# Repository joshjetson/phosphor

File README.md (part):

<p align="center">

</p>

<p align="center">
  <strong>A terminal-native DAW built in Rust</strong><br/>
  9 built-in synthesizers, 18 drum kits, a sampler, 1,531 patches, 9 color themes, animated splash screen, session save/load, undo/redo, and a plugin system designed for extensibility.
</p>

<p align="center">
  <br/>
  <sub><em>an animated impression of the track view — the real thing runs in your terminal:</em></sub>
</p>

---

## Index

- [Overview](#overview)
- [Quick Start](#quick-start)
- [Instruments](#instruments)
- [Features](#features)
- [Sampler — a sound on every key](#sampler--a-sound-on-every-key)
- [Fingers — the practice room](#fingers--the-practice-room)
- [The Phosphor Deck — an optional controller](#the-phosphor-deck--an-optional-controller)
- [Shortcuts, A to Z](#shortcuts-a-to-z)
- [Controls](#controls)
- [Themes](#themes)
- [Architecture](#architecture)
- [Building from Source](#building-from-source)
- [Project Structure](#project-structure)
- [Configuration](#configuration)
- [Contributing](#contributing)
- [License](#license)

---

## Overview

Phosphor is a digital audio workstation that runs entirely in your terminal. It pairs a themeable TUI with a real-time audio engine, giving you a DAW you can use over SSH, in a tiling window manager, or anywhere a terminal lives.

Each instrument track gets its own synthesizer instance with independent parameters. Every MIDI device you plug in is used at once, including ones plugged in while it runs. The audio engine runs on a dedicated real-time thread with lock-free communication — no mutexes in the audio path, ever.

---

## Quick Start

Phosphor runs on Windows, macOS and Linux. Everything is installed with
one command — but that command needs the Rust toolchain, and each
platform has one thing to do first. Start with yours:

**Windows** — install Rust from [rustup.rs](https://rustup.rs). The
installer will say it needs the Visual Studio C++ Build Tools and offer
to set them up — say yes; Rust compiles through them on Windows and
nothing works without them. Then open **Windows Terminal** (built into
Windows 11, free in the Microsoft Store on 10) rather than the old
Command Prompt: Phosphor draws its keyboards, meters and braces in
Unicode, and the legacy console mangles them. Audio and MIDI work out of
the box. Your files land in `%APPDATA%\phosphor`.

**macOS** — if you have never compiled anything on this machine, run
`xcode-select --install` once and let it finish. Then install Rust from
[rustup.rs](https://rustup.rs). Your files land in `~/.phosphor`.

**Linux** — install Rust from [rustup.rs](https://rustup.rs), plus the
ALSA headers the audio layer compiles against — without them the install
command fails halfway with a wall of C errors. Debian/Ubuntu:
`sudo apt install build-essential pkg-config libasound2-dev`. Fedora:
`sudo dnf install alsa-lib-devel`. Arch: `sudo pacman -S alsa-lib`.
Your files land in `~/.phosphor`.

Then, on every platform, the same command — and after it finishes, the
program is simply `phosphor` in your terminal:

```bash
# Install from crates.io — the --locked flag is required. It builds with
# the exact dependency versions the release was tested with; without it
# cargo picks newer ones, which now demand a newer Rust than the crate's,
# and the build fails.
cargo install phosphor-studio --locked

# Then run it
phosphor

# Or clone and build — this is how to get the newest version, which may
# be ahead of the one published on crates.io
git clone https://github.com/joshjetson/phosphor.git
cd phosphor
cargo install --path . --locked

# Run (TUI is the default)
cargo run --release

# Run with debug logging (PowerShell on Windows:
#   $env:PHOSPHOR_DEBUG=1; cargo run --release)
PHOSPHOR_DEBUG=1 cargo run --release

# Run without audio (UI development)
cargo run --release -- --no-audio

# Run without MIDI
cargo run --release -- --no-midi
```

**First steps once running:**

1. Press `Space` to open the command menu
2. Press `a` to add an instrument track
3. Select an instrument and press `Enter`
4. Play your MIDI controller — sound comes out
5. Use `j/k` to navigate synth parameters, `h/l` to adjust values — the
   first one is the patch selector
6. Press `Tab` to reach `[inst]`, the instrument's full panel, laid out in
   columns with room for all of it; `Tab` again for the piano roll
7. Press `Space` then `v` to change the color theme

### Plugging in MIDI gear

Plug in as many MIDI keyboards and controllers as you like — Phosphor
listens to all of them at once. You can plug one in or pull it out while
Phosphor is running: within a couple of seconds the bottom bar says
`MIDI: <name> connected` (or `unplugged`), and it just works. Nothing to set
up, no restart.

### Staying up to date

The first time you run a version you have not seen, phosphor shows a
**what's new** card — a short note on what changed, scrollable with `j`/`k`,
closed with `Esc` or `Enter`. It reads the same summaries kept in
[`CHANGELOG.md`](CHANGELOG.md).

Phosphor also checks crates.io in the background — at most once every six
hours, and silently if you are offline — and if a newer version is published
it shows a single line in the bottom bar telling you the one command that
updates it: `cargo install phosphor-studio --locked`. Press `Esc` at the track
list to dismiss it. To turn the check off entirely, set
`PHOSPHOR_NO_UPDATE_CHECK=1` in your environment.

### Will my computer keep up? — `phosphor --benchmark`

Run `phosphor --benchmark` on any computer — a laptop, a Raspberry Pi —
before you rely on it for music. It plays a busy song (every instrument,
effects, sends and a loop recording) through Phosphor's real sound engine
for about half a minute, first on one core and then on all of them, and
times every block of sound against the time it has. Then it says, in a
sentence, whether that computer has plenty of room, keeps up, or will
break up on a song that heavy. Close other busy programs first: anything
else using the processor makes the result look worse than it is.

---

## Instruments

### Synthesizers

| Instrument | Type | Voices | Patches | Description |
|-----------|------|--------|---------|-------------|
| **Phosphor Synth** | Wavetable / vector | 8 | **229** | Four oscillators with vector mixing, 16 wavetables, per-oscillator wave sequencing, Moog-style ladder, 6-slot mod matrix, keymapped drum patches |
| **DX7** | FM | 16 | **256** | All 8 original factory cartridges, decoded from the ROM dumps |
| **Jupiter-8** | Analog poly | 8 | **64** | All 64 factory patch names, full 32-control panel, two envelopes |
| **ARP Odyssey** | Duophonic | 2 | 44 | Complete 59-control front panel, all three filter revisions (4023/4035/4075), ADSR *and* AR envelopes, sample and hold |
| **Rhodes** | Physical model | 16 | 26 | Tine and tonebar as a coupled fork, inharmonic cantilever modes, nonlinear magnetic pickup |
| **Juno-60** | DCO poly | 6 | **56** | All 56 factory patches, read off Roland's patch charts; complete 25-control front panel measured against the hardware |
| **Little Phatty** | Mono Moog | 1 | **100** | Continuously morphing oscillators (triangle→saw→square→pulse, band-limited at every position in between), hard sync, 1/2/3/4-pole ladder, pre- and post-filter overload, the one-bus mod matrix with its spare destination, glide, and the three keyboard priorities |
| **Prophet-6** | Analog poly | 6 | **500** | All 500 factory programs, decoded from Sequential's own SysEx. Morphing oscillators with a triangle sub, resonant high-pass *and* SSM2040-lineage low-pass in series, poly mod (filter envelope and oscillator 2 into oscillator 1's frequency, shape and width and into both filters, at audio rate), per-oscillator slop, unison with chord memory, aftertouch, analog distortion |
| **TEO-5** | Analog poly | 5 | **256** | All 256 factory programs, decoded from Oberheim's own SysEx. The SEM state-variable filter, whose state control morphs continuously from low pass through notch to high pass with band pass on a switch; through-zero FM between the oscillators; three independently mixable waveshapes each, hard sync, a square sub and white or pink noise; two OB-8-curve DADSR envelopes; a global LFO and a per-voice one; a 16-slot modulation matrix of 20 sources against 65 destinations; twelve effect algorithms; unison with stored chord memory |

### Sampler

| Instrument | Type | Voices | Sounds | Description |
|-----------|------|--------|--------|-------------|
| **Sampler** | Sample playback | 64 | yours | 88 pads, one per piano key, eight sounds stacked on each with their own tune, trim, reverse and mute; per-pad trigger, poly, choke group, round robin, pitch, ADSR, level, pan, root and keytracking; a trim strip with a zero-crossing snap and a key that
hugs the sound; **keys mode**, where stretches of keys become chromatic zones playing one sound from a root; and resampling — record any instrument in the box onto a pad, free or cut to whole bars; and **chop** — cut a recording across the keys at its hits (kicks, snares or hats), on a beat grid, or into even slices |

64 is the number of voices allowed to sound at once, across the whole
instrument rather than per pad; the pool behind it holds 80, so a voice that
gets cut has somewhere to finish its fade. The per-pad limit is `poly`, which
runs 1–8 and counts *hits*.

### Drum Rack

| Kit | Character |
|-----|-----------|
| **808** | Rebuilt on the service-notes circuit values — 49.4 Hz bridged-T kick, 238/476 Hz snare, one shared free-running six-oscillator metal bank |
| **909** | The hybrid it really is — analog kick/snare/toms/rim/clap, and hi-hat, ride and crash as 6-bit 18 kHz samples |
| **707** | A PCM machine, not an analog one — sampled character through post-converter analog envelopes |
| **606** | Its own seven analog voices, built from the service-notes component values |
| **777** | 808/909 bass + creative FM/ring-mod/wavefolder sounds |
| **tsty-1** | Warm vintage, tape-saturated, reel-to-reel character |
| **tsty-2** | Acoustic modal — Bessel membrane modes, multi-phase envelopes |
| **tsty-3** | 88 unique sounds — every note a distinct synthesis |
| **tsty-4** | Extended hats/snares with long decays, varied synthesis methods |
| **tsty-5** | Resonator-based — impulse exciter into tuned bandpass filters, wire-coupled snares |
| **LinnDrum** | 15 recordings through a mu-255 companded 8-bit converter; tuning is the read clock, so pitch and length move together |
| **DMX** | 11 recordings making 15 sounds, companded 8-bit, per-card pitch trimmer at half an octave |
| **SDS-V** | Five analog modules — triangle VCO, noise and click through a 4-pole SSM2044, ramp VCAs that stop rather than fade |
| **727** | The 707's converter with the Latin voice set: congas, bongos, timbales, agogo, cabasa, maracas, whistles, quijada, star chime |
| **CR-78** | Pre-808 Roland analog — a snare with no oscillator in it at all, one LC band-pass for every metal voice, and the metallic beat |
| **jazz** | Live acoustic drums, modelled — a small bebop kit: sealed 18" kick with the two heads coupled through the shell, thin heads left to ring, a dark 20" ride, and brushes |
| **funk** | The same physics, a different drummer — 22" ported kick with a felt strip, a cranked snare over twenty tight strands, gel on the toms, and a ride with a ping |
| **studio** | Very dry and gated — a pillow in the kick that all but closes the two-head coupling, a muffling ring on the snare, taped toms, and a downward expander across every voice |

Past `studio`, the `kit` knob goes on into drum kits you made yourself on a
sampler — see [Your own drum kits](#your-own-drum-kits--spacew-on-a-sampler).

### Patch Highlights

**DX7** (256 voices): every voice from the eight original factory cartridges —
ROM1A/1B, ROM2A/2B, ROM3A/3B, ROM4A/4B — decoded from the ROM sysex dumps rather
than recreated. That includes the ones that defined the instrument: `E.PIANO 1`,
`BASS    1`, `TUB BELLS`, `BRASS   1`, `STRINGS 1`, `HARPSICH 1`, and the novelty
voices Yamaha shipped alongside them (`TAKE OFF`, `WASP STING`, `..GOTCHA..`).
Pick a cartridge with the `bank` parameter, then a voice with `patch`.

**Jupiter-8** (64 patches): the factory bank in Roland's own 8x8 numbering — `11 NEG SYNC`,
`13 JUICY FUNK`, `15 CARS SYNC`, `17 HAMMER LEAD`, `24 MELLOW RHODES`, `31 LO STRINGS`,
`45 PIPE ORGAN`, `51 TRAIN CHUG`, `57 TOMITA CHIME`, `63 KLINGONS`, `64 MUSIC OF THE SPHERES`,
`66 SOLAR WINDS`, `71 FAT FIFTHS`, `87 UPRIGHT BASS` and the rest. Names, numbers, voice modes
and character follow the original factory patch sheets; the parameter values are voiced to match
Roland's published description of each patch.

**Odyssey** (44 patches): Bass, Funk, Sync Lead, Bells, Pad, S&H, Zap, Hawkshaw Funk, Bennett Atmos, Numan Cars, Sci-Fi Wobble, Percussive Pluck, Thick Lead, Filter Sweep, Noise Hit, Duo Split, Snare Drum, Kick, Resonance, Squelch, Growl, Wind, Wah Bass, Stab, Buzz, Flute, Tremolo, Siren, Brass, Organ, Conga, Tom, Clap, PWM Bass, Violin, Oboe, Choir, Trombone, Marimba, Alarm, Robot, Whistler, Sitar, Theremin

**Juno-60** (56 factory patches, in the instrument's own seven banks of eight):

- **Bank 1** — 11 Strings 1, 12 Strings 2, 13 Strings 3, 14 Organ 1, 15 Organ 2, 16 Organ 3, 17 Brass, 18 Phase Brass
- **Bank 2** — 21 Piano 1, 22 Piano 2, 23 Celesta, 24 Mellow Piano, 25 Harpsichord 1, 26 Harpsichord 2, 27 Guitar, 28 Synthesizer Harp
- **Bank 3** — 31 Bass 1, 32 Bass 2, 33 Clavichord 1, 34 Clavichord 2, 35 Pizzicato Sound 1, 36 Pizzicato Sound 2, 37 Xylophone, 38 Glockenspeil
- **Bank 4** — 41 Violine, 42 Trumpet, 43 Horn, 44 Tuba, 45 Flute, 46 Clarinet, 47 Oboe, 48 English Horn
- **Bank 5** — 51 Funny Cat, 52 Wah Brass, 53 Phase Combination, 54 Reed 1, 55 Popcorn, 56 Reed 2, 57 Reed 3, 58 PWM Chorus
- **Bank 6** — 61 Synthesizer Organ, 62 Effect Sound 1, 63 Effect Sound 2, 64 Space Harp, 65 Funk, 66 Space Sound 1, 67 Mysterious Invention, 68 Space Sound 2
- **Bank 7** — 71 Percussive Sound 1, 72 Percussive Sound 2, 73 Whistle, 74 Effect Sound 3, 75 UFO, 76 Space Sound 3, 77 Surf, 78 Synthesizer Drum — the bank whose sound source is the VCF oscillating on its own

Names and spellings are Roland's, Glockenspeil included.

**Little Phatty** (100 patches, ours rather than Moog's — the Stage II's factory
*names* are printed in its manual but no published source gives the parameter
values behind them, so the bank is original and named in our own voice, weighted
towards bass the way the real one is):

- **Moog bass** — Taurus Deep, Sub Anchor, Round Bass, Bass Pillar, Thumb Bass, Wood Bass, Rubber Bass, Octave Bass, Muted Bass, Fifth Bass, Tri Sub, Pulse Bass, Sine Floor, Dub Weight, Slide Bass, Sequence Lo, Fat Unison, Bass Bloom
- **Overload** — Growl Bass, Tarmac, Coal Face, Snarl, Fuzz Anchor, Grit Stack, Overdriven, Bark Bass, Diesel, Torn Paper, Anvil Bass, Bad Weather
- **Sync** — Sync Lead, Sync Scream, Sync Sweep, Hard Reset, Sync Bell, Sync Buzz, Sync Whistle, Sync Stab
- **Lead** — Solo Saw, Reed Lead, Glass Lead, Whistle Top, Portamento, Brass Lead, Ribbon Lead, Flute Solo, Nasal Lead, Octave Lead, Vox Lead, Cut Lead
- **Wave morph** — Morph Drift, Half Saw, Between, Wave Wash, Slow Morph, Pulse Width, PWM Strings, Thin Ice, Wave Chase, Shape Shift, Morph Bass, Tri To Saw
- **Sample and hold, and effects** — Random Steps, Sample Hold, Computer, Alarm, Siren, Radio Chirp, Wind Tunnel, Static, Bleep Bloop, Sonar
- **Slope** — 2 Pole Bass, 1 Pole Pad, Open Ladder, Leaky, Bright 12dB, 6dB Lead, Half Ladder, Slope Swap
- **Pluck and percussion** — Zap Pluck, Clav Pluck, Wood Block, Kick Drum, Tom Hit, Blip, Marimba, Snap Bass, Dry Tick, Bell Pluck
- **Drone** — Self Osc, Slow Swell, Held Tone, Deep Drone, Air Pad, Ghost Pad, Filter Wash, Long Fifth, Choir Mono, Night Hum

**Rhodes** (26 patches, by instrument rather than by factory number — a Rhodes
has no patch memory):

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
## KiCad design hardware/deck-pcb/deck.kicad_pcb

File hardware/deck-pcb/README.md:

# Phosphor Deck controller board

The circuit board for the Phosphor Deck: every knob, button, fader and pad on
top, and the electronics that read them underneath. It is the board drawn on
the schematics, and it runs the firmware in [`../../firmware`](../../firmware).

**Rev A has not been made yet.** It passes KiCad's design-rule check with no
errors and no unconnected pins, but nobody has held one. Build the breadboard
test in the firmware's README before ordering.

## What to send a board house

Everything is in `fab/`:

- `gerbers.zip` — the board itself: two copper layers, 296 × 234 mm, 1.6 mm.
- `bom.csv` — every part, grouped, with the part to buy where there is one.
- `positions-bottom.csv` — where each surface-mount part goes, for a house
  that assembles the underside.
- `jlc-bom.csv` and `jlc-cpl.csv` — the same parts and places in the exact
  form JLCPCB asks for, with their LCSC part numbers.

The board is laid out so that a board house only has to assemble one side:
every surface-mount part (chips, resistors, capacitors, LEDs, the Pico 2) is
on the bottom. Everything on top is through-hole and soldered by hand: 61
switches, 10 knobs, 8 faders, the 16 pad sensors' tabs and the pedal header.

## Ordering from JLCPCB, step by step

JLCPCB makes the board and solders every part on the underside for you. You
then solder the top parts by hand.

1. **Upload the board.** On jlcpcb.com, choose *Order now* and add
   `fab/gerbers.zip`. It reads the size (296 × 234 mm) and the two layers by
   itself.
2. **Choose the board options.** Layers 2, thickness 1.6 mm, FR-4. Five
   boards is the smallest order. Green is the cheapest colour; any colour
   works. For the surface finish, lead-free HASL is fine; ENIG costs more
   and gives flatter pads. Leave the rest as it is.
3. **Turn on PCB Assembly.** Choose:
   - *PCBA type: Standard.* Economic is cheaper, but it is meant for one
     side, usually the top, and JLC sells the Pico 2 for Standard only. If
     Economic offers *Bottom Side* when you order and you will solder the
     Pico yourself, Economic works too.
   - *Assembly side: Bottom Side.* Every machine part is underneath.
   - *Assembly quantity:* 2 or more; it can be fewer than the boards.
   - Let JLC add the edge rails, fiducials and tooling holes if it asks.
     Standard assembly needs them and the board has none of its own.
   - Tick *Confirm parts placement*: for a small fee, one of their engineers
     checks the placements and asks you before building.
4. **Upload the two parts files**: `fab/jlc-bom.csv` as the BOM and
   `fab/jlc-cpl.csv` as the CPL (the placement file). Every line should
   match a part. If one is out of stock, pick a part with the same value,
   rating and size, or wait.
5. **Check the placement preview.** It shows each part on the board, seen
   from underneath. The files already turn each part the way JLC's drawings
   need, but look at each kind once:
   - the chips (U1–U16): the dot that marks pin 1 sits on the board's pin-1
     mark;
   - the LEDs (D1–D42): the LED's cut corner matches its outline, and the
     body sits over the light hole;
   - the big capacitor (C79): its + side sits on the + pad;
   - the Pico 2 (U15): its USB socket is at the same end as on the board
     drawing.

   The small resistors and capacitors can sit either way round. If a part
   is wrong, select it and turn it in the preview, or change its *Rotation*
   in `jlc-cpl.csv` and upload it again.
6. **Solder the top by hand** when the boards arrive: the 61 switches, 10
   knobs, 8 faders, the 16 pad sensors' tabs and the pedal header. If you
   left the Pico 2 off the order (mark it *do not place* on the parts page),
   solder it underneath by its edge pads.

The board is larger than 650 cm², so JLC adds a large-board fee to the
assembly. Basic parts need no loading fee in an Economic order; in a
Standard order every kind of part has a small one.

## Things to know before ordering

- **The LED light holes.** The LEDs sit underneath and shine up through small
  holes. KiCad's own footprint for them puts their pads 0.25 mm from the
  hole's corners; the rest of the board keeps 0.3 mm. Most board houses accept
  this for internal cutouts — ask yours.
- **The buttons are 6 × 6 mm tactile switches** under printed caps, because
  the panel's buttons sit closer together than keyboard switches allow. Pick
  the switch height that meets your caps through the top plate.
- **The faders are centred at 167 mm**, 2 mm lower than the first panel
  drawing: a PTA4543's body is 60 mm long. The top plate's slots run from
  143 to 191 mm.
- **Lights on narrow buttons are dots.** The transport and function buttons
  are too narrow for a light inside the cap, so theirs sits just above as a
  dot in the top plate.
- **The Pico 2 is soldered flat by its edges** on the underside. Its USB
  socket points along the board, so use a right-angle micro-USB cable to the
  Raspberry Pi.

## Making it again

The board is generated, not drawn: `generate.py` places every part from the
panel drawing and wires it from `firmware/deck-layout.json`, Phosphor's own
control table, so the board, the firmware and the app share one table.
`route.sh` runs the lot — placement, routing with Freerouting, ground pours,
the design-rule check, and the files in `fab/`:

```
KICAD=/Applications/KiCad/KiCad.app \
FREEROUTING=freerouting-2.4.1.jar \
JAVA=<a Java 25 runtime>/bin/java \
./route.sh
```

It needs KiCad 10 and Freerouting 2.4, which needs Java 25. Routing takes
about five minutes a try. The router's result varies a little from run to
run and now and then leaves a connection unrouted, so the script tries up to
three times and writes `fab/` only from a board with no errors and nothing
unconnected; `drc.rpt` is the check that board passed. A ground fill covers
both sides, tied together by stitching vias wherever one fits.

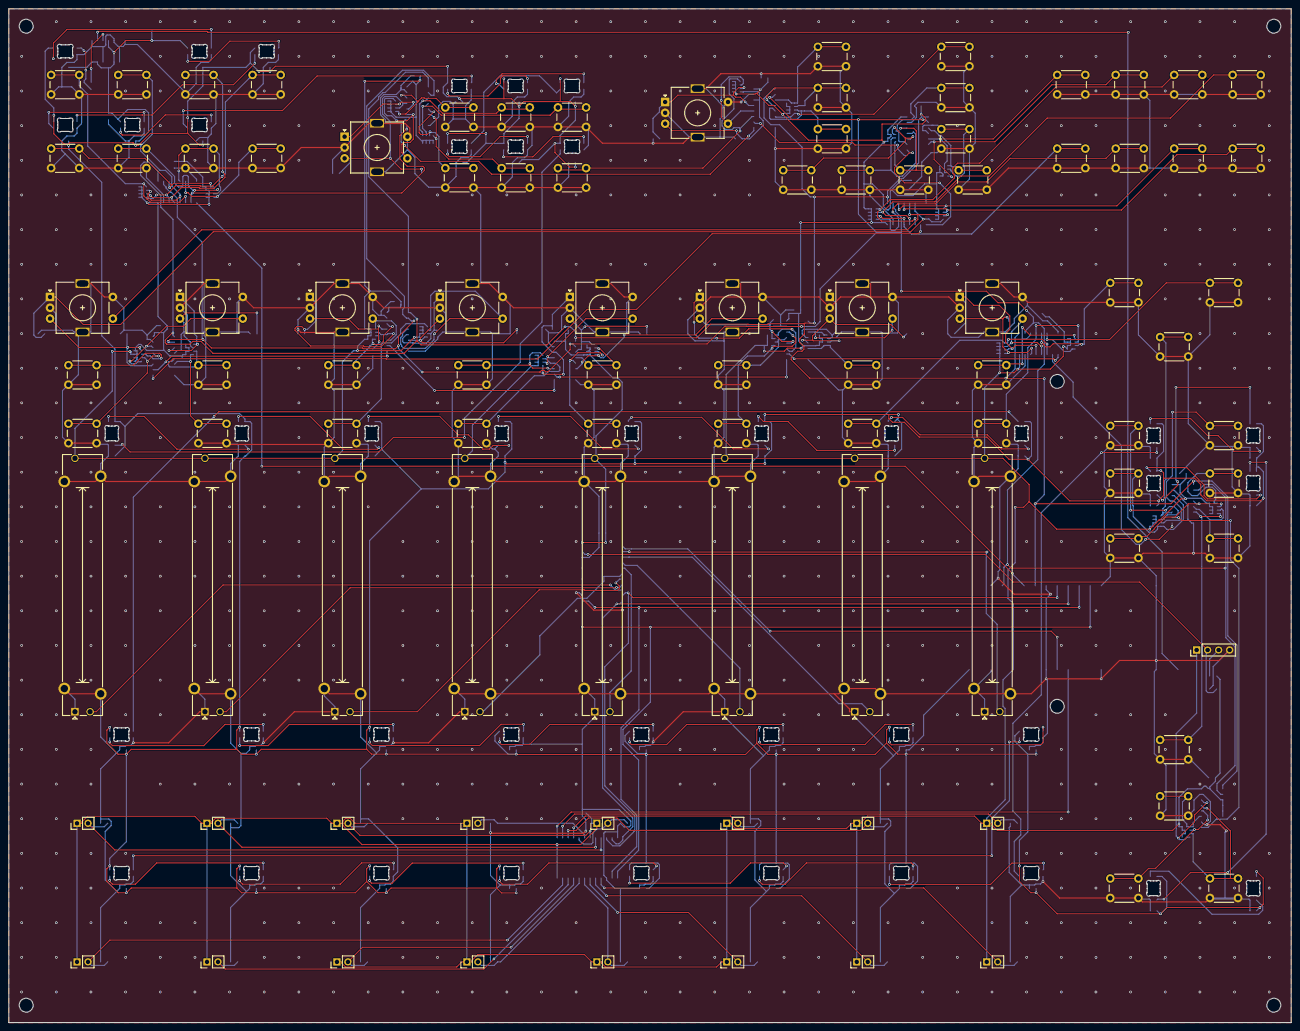
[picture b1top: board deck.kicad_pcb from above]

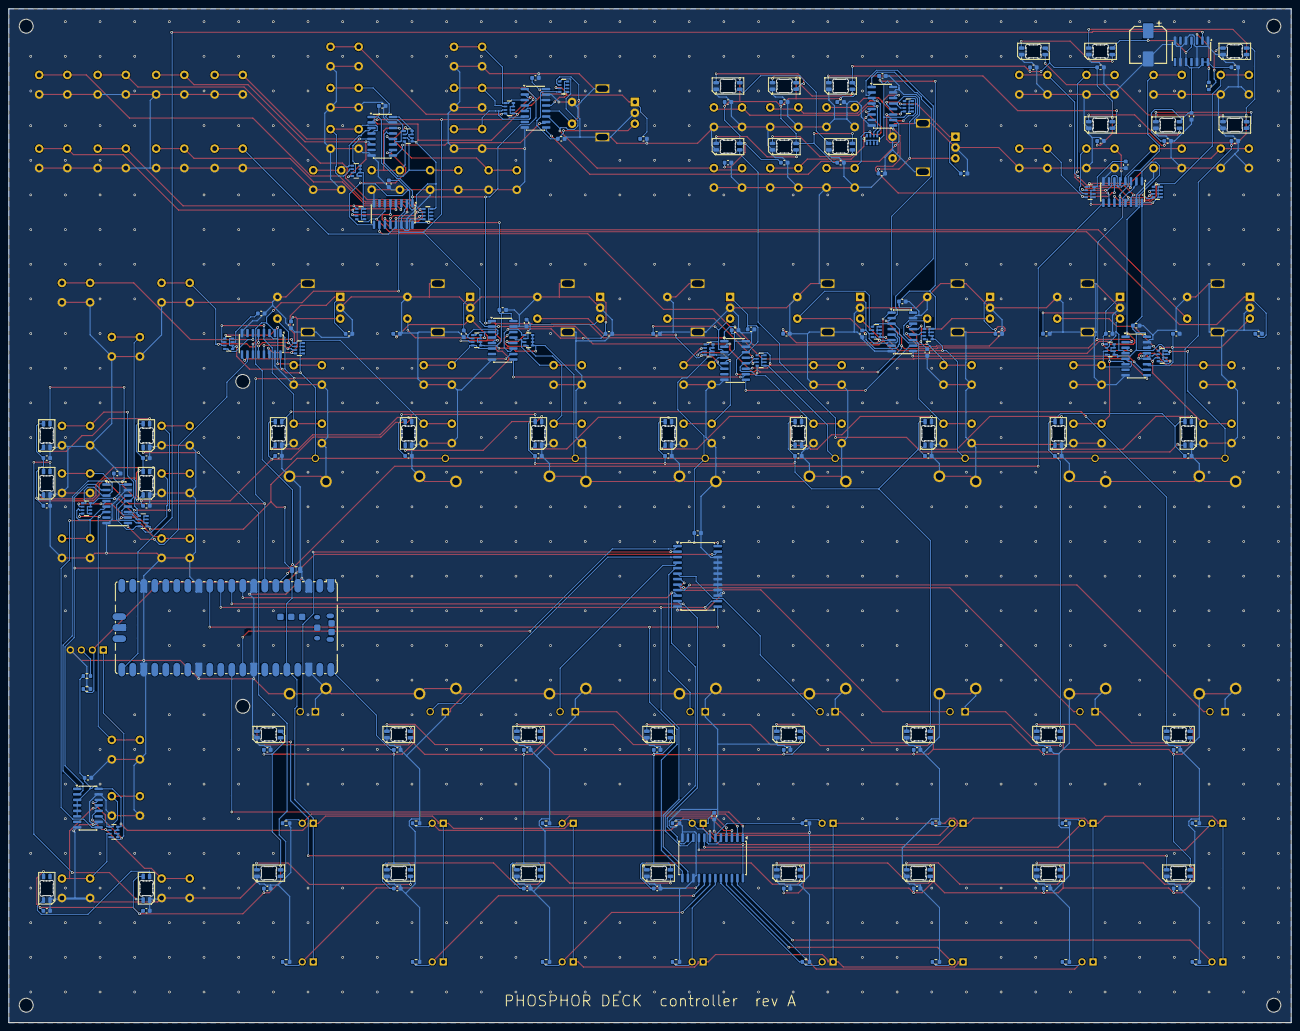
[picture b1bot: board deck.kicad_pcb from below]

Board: 2 copper layers, 296.0 x 234.0 mm, 281 parts (179 on the bottom side), 185 nets.

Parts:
C1, C2, C3, C4, C5, C6, C7, C8, C9, C10, C11, C12, C13, C14, C15, C16, C17, C18, C19, C20, C21, C22, C23, C24, C25, C26, C27, C28, C29, C30, C31, C32, C33, C34, C35, C36, C37, C38, C39, C40, C41, C42, C43, C44, C45, C46, C47, C48, C49, C50, C51, C52, C53, C54, C75, C76, C78: 100n; C_0603_1608Metric
C55, C56, C57, C58, C59, C60, C61, C62, C63, C64, C65, C66, C67, C68, C69, C70, C71, C72, C73, C74: 10n; C_0603_1608Metric
C77: 10u; C_0805_2012Metric
C79: 1000u 10V; CP_Elec_8x10
D1, D2, D3, D4, D5, D6, D7, D8, D9, D10, D11, D12, D13, D14, D15, D16, D17, D18, D19, D20, D21, D22, D23, D24, D25, D26, D27, D28, D29, D30, D31, D32, D33, D34, D35, D36, D37, D38, D39, D40, D41, D42: SK6812MINI-E; LED_SK6812MINI-E_3.2x2.8mm_P1.5mm_ReverseMount
ENC1: FUNCTION; RotaryEncoder_Alps_EC11E-Switch_Vertical_H20mm
ENC2: NAVIGATE; RotaryEncoder_Alps_EC11E-Switch_Vertical_H20mm
ENC3: KNOB 1; RotaryEncoder_Alps_EC11E-Switch_Vertical_H20mm
ENC4: KNOB 2; RotaryEncoder_Alps_EC11E-Switch_Vertical_H20mm
ENC5: KNOB 3; RotaryEncoder_Alps_EC11E-Switch_Vertical_H20mm
ENC6: KNOB 4; RotaryEncoder_Alps_EC11E-Switch_Vertical_H20mm
ENC7: KNOB 5; RotaryEncoder_Alps_EC11E-Switch_Vertical_H20mm
ENC8: KNOB 6; RotaryEncoder_Alps_EC11E-Switch_Vertical_H20mm
ENC9: KNOB 7; RotaryEncoder_Alps_EC11E-Switch_Vertical_H20mm
ENC10: KNOB 8; RotaryEncoder_Alps_EC11E-Switch_Vertical_H20mm
FSR1: PAD 1; PinHeader_1x02_P2.54mm_Vertical
FSR2: PAD 2; PinHeader_1x02_P2.54mm_Vertical
FSR3: PAD 3; PinHeader_1x02_P2.54mm_Vertical
FSR4: PAD 4; PinHeader_1x02_P2.54mm_Vertical
FSR5: PAD 5; PinHeader_1x02_P2.54mm_Vertical
FSR6: PAD 6; PinHeader_1x02_P2.54mm_Vertical
FSR7: PAD 7; PinHeader_1x02_P2.54mm_Vertical
FSR8: PAD 8; PinHeader_1x02_P2.54mm_Vertical
FSR9: PAD 9; PinHeader_1x02_P2.54mm_Vertical
FSR10: PAD 10; PinHeader_1x02_P2.54mm_Vertical
FSR11: PAD 11; PinHeader_1x02_P2.54mm_Vertical
FSR12: PAD 12; PinHeader_1x02_P2.54mm_Vertical
FSR13: PAD 13; PinHeader_1x02_P2.54mm_Vertical
FSR14: PAD 14; PinHeader_1x02_P2.54mm_Vertical
FSR15: PAD 15; PinHeader_1x02_P2.54mm_Vertical
FSR16: PAD 16; PinHeader_1x02_P2.54mm_Vertical
H1, H2, H3, H4, H5, H6: M3; MountingHole_3.2mm_M3
J1: PEDALS; PinHeader_1x04_P2.54mm_Vertical
R1, R2, R3, R4, R5, R6, R7, R8, R9, R10, R11, R12, R13, R14, R15, R16: 10k; R_0603_1608Metric
R17: 1k; R_0603_1608Metric
R18: 100k; R_0603_1608Metric
R19: 330; R_0603_1608Metric
RN1, RN2, RN3, RN4, RN5, RN6, RN7, RN8, RN9, RN10, RN11, RN12, RN13, RN14, RN15, RN16, RN17, RN18, RN19, RN20, RN21, RN22, RN23: 4x10k; R_Array_Convex_4x0603
RV1: FADER 1; Potentiometer_Bourns_PTA4543_Single_Slide
RV2: FADER 2; Potentiometer_Bourns_PTA4543_Single_Slide
RV3: FADER 3; Potentiometer_Bourns_PTA4543_Single_Slide
RV4: FADER 4; Potentiometer_Bourns_PTA4543_Single_Slide
RV5: FADER 5; Potentiometer_Bourns_PTA4543_Single_Slide
RV6: FADER 6; Potentiometer_Bourns_PTA4543_Single_Slide
RV7: FADER 7; Potentiometer_Bourns_PTA4543_Single_Slide
RV8: FADER 8; Potentiometer_Bourns_PTA4543_Single_Slide
SW1: PLAY; SW_PUSH_6mm
SW2: STOP; SW_PUSH_6mm
SW3: REC; SW_PUSH_6mm
SW4: OVERDUB; SW_PUSH_6mm
SW5, SW13: LOOP; SW_PUSH_6mm
SW6: CLICK; SW_PUSH_6mm
SW7: COUNT IN; SW_PUSH_6mm
SW8: TAP; SW_PUSH_6mm
SW9: TEMPO; SW_PUSH_6mm
SW10: SWING; SW_PUSH_6mm
SW11: GRID; SW_PUSH_6mm
SW12: MASTER; SW_PUSH_6mm
SW14: LAST; SW_PUSH_6mm
SW15: LOCK; SW_PUSH_6mm
SW16: BACK; SW_PUSH_6mm
SW17: BROWSE; SW_PUSH_6mm
SW18: SHIFT; SW_PUSH_6mm
SW19: MENU; SW_PUSH_6mm
SW20: LEFT; SW_PUSH_6mm
SW21: UP; SW_PUSH_6mm
SW22: DOWN; SW_PUSH_6mm
SW23: RIGHT; SW_PUSH_6mm
SW24: PART; SW_PUSH_6mm
SW25: UNDO; SW_PUSH_6mm
SW26: REDO; SW_PUSH_6mm
SW27: COPY; SW_PUSH_6mm
SW28: PASTE; SW_PUSH_6mm
SW29: DELETE; SW_PUSH_6mm
SW30: DUPLICATE; SW_PUSH_6mm
SW31: SAVE; SW_PUSH_6mm
SW32: NEW; SW_PUSH_6mm
SW33: ACTION 1; SW_PUSH_6mm
SW34: T1; SW_PUSH_6mm
SW35: ACTION 2; SW_PUSH_6mm
SW36: T2; SW_PUSH_6mm
SW37: ACTION 3; SW_PUSH_6mm
SW38: T3; SW_PUSH_6mm
SW39: ACTION 4; SW_PUSH_6mm
SW40: T4; SW_PUSH_6mm
SW41: ACTION 5; SW_PUSH_6mm
SW42: T5; SW_PUSH_6mm
SW43: ACTION 6; SW_PUSH_6mm
SW44: T6; SW_PUSH_6mm
SW45: ACTION 7; SW_PUSH_6mm
SW46: T7; SW_PUSH_6mm
SW47: ACTION 8; SW_PUSH_6mm
SW48: T8; SW_PUSH_6mm
SW49: ◀ PG; SW_PUSH_6mm
SW50: PG ▶; SW_PUSH_6mm
SW51: MY PAGE; SW_PUSH_6mm
SW52: SELECT; SW_PUSH_6mm
SW53: MUTE; SW_PUSH_6mm
SW54: SOLO; SW_PUSH_6mm
SW55: ARM; SW_PUSH_6mm
SW56: ◀ TRK; SW_PUSH_6mm
SW57: TRK ▶; SW_PUSH_6mm
SW58: PADS ▲; SW_PUSH_6mm
SW59: PADS ▼; SW_PUSH_6mm
SW60: 1-16; SW_PUSH_6mm
SW61: 17-32; SW_PUSH_6mm
U1, U2, U3, U4, U5, U6, U7, U8, U9, U10, U11, U12: 74HC165; SOIC-16_3.9x9.9mm_P1.27mm
U13, U14: 74HC4067; SOIC-24W_7.5x15.4mm_P1.27mm
U15: Pico 2; RaspberryPi_Pico_SMD
U16: 74AHCT125; SOIC-14_3.9x8.7mm_P1.27mm

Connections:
+3V3: C43.1, C44.1, C45.1, C46.1, C47.1, C48.1, C49.1, C50.1, C51.1, C52.1, C53.1, C54.1, C75.1, C76.1, C77.1, FSR1.1, FSR2.1, FSR3.1, FSR4.1, FSR5.1, FSR6.1, FSR7.1, FSR8.1, FSR9.1, FSR10.1, FSR11.1, FSR12.1, FSR13.1, FSR14.1, FSR15.1, FSR16.1, R17.1, RN1.5, RN1.6, RN1.7, RN1.8, RN2.5, RN2.6, RN2.7, RN2.8, RN3.5, RN3.6, RN3.7, RN3.8, RN4.5, RN4.6, RN4.7, RN4.8, RN5.5, RN5.6, RN5.7, RN5.8, RN6.5, RN6.6, RN6.7, RN6.8, RN7.5, RN7.6, RN7.7, RN7.8, RN8.5, RN8.6, RN8.7, RN8.8, RN9.5, RN9.6, RN9.7, RN9.8, RN10.5, RN10.6, RN10.7, RN10.8, RN11.5, RN11.6, RN11.7, RN11.8, RN12.5, RN12.6, RN12.7, RN12.8, RN13.5, RN13.6, RN13.7, RN13.8, RN14.5, RN14.6, RN14.7, RN14.8, RN15.5, RN15.6, RN15.7, RN15.8, RN16.5, RN16.6, RN16.7, RN16.8, RN17.5, RN17.6, RN17.7, RN17.8, RN18.5, RN18.6, RN18.7, RN18.8, RN19.5, RN19.6, RN19.7, RN19.8, RN20.5, RN20.6, RN20.7, RN20.8, RN21.5, RN21.6, RN21.7, RN21.8, RN22.5, RN22.6, RN22.7, RN22.8, RN23.5, RN23.6, RN23.7, RN23.8, RV1.3, RV2.3, RV3.3, RV4.3, RV5.3, RV6.3, RV7.3, RV8.3, U1.16, U2.16, U3.16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
+5V: C1.1, C2.1, C3.1, C4.1, C5.1, C6.1, C7.1, C8.1, C9.1, C10.1, C11.1, C12.1, C13.1, C14.1, C15.1, C16.1, C17.1, C18.1, C19.1, C20.1, C21.1, C22.1, C23.1, C24.1, C25.1, C26.1, C27.1, C28.1, C29.1, C30.1, C31.1, C32.1, C33.1, C34.1, C35.1, C36.1, C37.1, C38.1, C39.1, C40.1, C41.1, C42.1, C78.1, C79.1, D1.3, D2.3, D3.3, D4.3, D5.3, D6.3, D7.3, D8.3, D9.3, D10.3, D11.3, D12.3, D13.3, D14.3, D15.3, D16.3, D17.3, D18.3, D19.3, D20.3, D21.3, D22.3, D23.3, D24.3, D25.3, D26.3, D27.3, D28.3, D29.3, D30.3, D31.3, D32.3, D33.3, D34.3, D35.3, D36.3, D37.3, D38.3, D39.3, D40.3, D41.3, D42.3, U15.40, U16.4, U16.10, U16.13, U16.14
CHAIN1: U1.10, U2.9
CHAIN2: U2.10, U3.9
CHAIN3: U3.10, U4.9
CHAIN4: U4.10, U5.9
CHAIN5: U5.10, U6.9
CHAIN6: U6.10, U7.9
CHAIN7: U7.10, U8.9
CHAIN8: U8.10, U9.9
CHAIN9: U9.10, U10.9
CHAIN10: U10.10, U11.9
CHAIN11: U11.10, U12.9
EXPR: J1.2, R18.1, U14.23
EXPR_RING: J1.3, R17.2
FADER0: RV1.2, U14.9
FADER1: RV2.2, U14.8
FADER2: RV3.2, U14.7
FADER3: RV4.2, U14.6
FADER4: RV5.2, U14.5
FADER5: RV6.2, U14.4
FADER6: RV7.2, U14.3
FADER7: RV8.2, U14.2
FADERS_ADC: U14.1, U15.32
GND: C1.2, C2.2, C3.2, C4.2, C5.2, C6.2, C7.2, C8.2, C9.2, C10.2, C11.2, C12.2, C13.2, C14.2, C15.2, C16.2, C17.2, C18.2, C19.2, C20.2, C21.2, C22.2, C23.2, C24.2, C25.2, C26.2, C27.2, C28.2, C29.2, C30.2, C31.2, C32.2, C33.2, C34.2, C35.2, C36.2, C37.2, C38.2, C39.2, C40.2, C41.2, C42.2, C43.2, C44.2, C45.2, C46.2, C47.2, C48.2, C49.2, C50.2, C51.2, C52.2, C53.2, C54.2, C55.2, C56.2, C57.2, C58.2, C59.2, C60.2, C61.2, C62.2, C63.2, C64.2, C65.2, C66.2, C67.2, C68.2, C69.2, C70.2, C71.2, C72.2, C73.2, C74.2, C75.2, C76.2, C77.2, C78.2, C79.2, D1.1, D2.1, D3.1, D4.1, D5.1, D6.1, D7.1, D8.1, D9.1, D10.1, D11.1, D12.1, D13.1, D14.1, D15.1, D16.1, D17.1, D18.1, D19.1, D20.1, D21.1, D22.1, D23.1, D24.1, D25.1, D26.1, D27.1, D28.1, D29.1, D30.1, D31.1, D32.1, D33.1, D34.1, D35.1, D36.1, D37.1, D38.1, D39.1, D40.1, D41.1, D42.1, ENC1.C, ENC1.MP, ENC1.S2, ENC2.C, ENC2.MP, ENC2.S2, ENC3.C, ENC3.MP, ENC3.S2, ENC4.C, ENC4.MP, ENC4.S2, ENC5.C, ENC5.MP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
IN0: RN1.1, SW1.1, U1.11
IN1: RN1.2, SW2.1, U1.12
IN2: RN1.3, SW3.1, U1.13
IN3: RN1.4, SW4.1, U1.14
IN4: RN2.1, SW5.1, U1.3
IN5: RN2.2, SW6.1, U1.4
IN6: RN2.3, SW7.1, U1.5
IN7: RN2.4, SW8.1, U1.6
IN8: ENC1.S1, RN3.1, U2.11
IN9: C55.1, ENC1.A, RN3.2, U2.12
IN10: C56.1, ENC1.B, RN3.3, U2.13
IN11: RN3.4, SW9.1, U2.14
IN12: RN4.1, SW10.1, U2.3
IN13: RN4.2, SW11.1, U2.4
IN14: RN4.3, SW12.1, U2.5
IN15: RN4.4, SW13.1, U2.6
IN16: RN5.1, SW14.1, U3.11
IN17: ENC2.S1, RN5.2, U3.12
IN18: C57.1, ENC2.A, RN5.3, U3.13
IN19: C58.1, ENC2.B, RN5.4, U3.14
IN20: RN6.1, SW15.1, U3.3
IN21: RN6.2, SW16.1, U3.4
IN22: RN6.3, SW17.1, U3.5
IN23: RN6.4, SW18.1, U3.6
IN24: RN7.1, SW19.1, U4.11
IN25: RN7.2, SW20.1, U4.12
IN26: RN7.3, SW21.1, U4.13
IN27: RN7.4, SW22.1, U4.14
IN28: RN8.1, SW23.1, U4.3
IN29: RN8.2, SW24.1, U4.4
IN30: RN8.3, SW25.1, U4.5
IN31: RN8.4, SW26.1, U4.6
IN32: RN9.1, SW27.1, U5.11
IN33: RN9.2, SW28.1, U5.12
IN34: RN9.3, SW29.1, U5.13
IN35: RN9.4, SW30.1, U5.14
IN36: RN10.1, SW31.1, U5.3
IN37: RN10.2, SW32.1, U5.4
IN38: ENC3.S1, RN10.3, U5.5
IN39: C59.1, ENC3.A, RN10.4, U5.6
IN40: C60.1, ENC3.B, RN11.1, U6.11
IN41: RN11.2, SW33.1, U6.12
IN42: RN11.3, SW34.1, U6.13
IN43: ENC4.S1, RN11.4, U6.14
IN44: C61.1, ENC4.A, RN12.1, U6.3
IN45: C62.1, ENC4.B, RN12.2, U6.4
IN46: RN12.3, SW35.1, U6.5
IN47: RN12.4, SW36.1, U6.6
IN48: ENC5.S1, RN13.1, U7.11
IN49: C63.1, ENC5.A, RN13.2, U7.12
IN50: C64.1, ENC5.B, RN13.3, U7.13
IN51: RN13.4, SW37.1, U7.14
IN52: RN14.1, SW38.1, U7.3
IN53: ENC6.S1, RN14.2, U7.4
IN54: C65.1, ENC6.A, RN14.3, U7.5
IN55: C66.1, ENC6.B, RN14.4, U7.6
IN56: RN15.1, SW39.1, U8.11
IN57: RN15.2, SW40.1, U8.12
IN58: ENC7.S1, RN15.3, U8.13
IN59: C67.1, ENC7.A, RN15.4, U8.14
IN60: C68.1, ENC7.B, RN16.1, U8.3
IN61: RN16.2, SW41.1, U8.4
IN62: RN16.3, SW42.1, U8.5
IN63: ENC8.S1, RN16.4, U8.6
IN64: C69.1, ENC8.A, RN17.1, U9.11
IN65: C70.1, ENC8.B, RN17.2, U9.12
IN66: RN17.3, SW43.1, U9.13
IN67: RN17.4, SW44.1, U9.14
IN68: ENC9.S1, RN18.1, U9.3
IN69: C71.1, ENC9.A, RN18.2, U9.4
IN70: C72.1, ENC9.B, RN18.3, U9.5
IN71: RN18.4, SW45.1, U9.6
IN72: RN19.1, SW46.1, U10.11
IN73: ENC10.S1, RN19.2, U10.12
IN74: C73.1, ENC10.A, RN19.3, U10.13
IN75: C74.1, ENC10.B, RN19.4, U10.14
IN76: RN20.1, SW47.1, U10.3
IN77: RN20.2, SW48.1, U10.4
IN78: RN20.3, SW49.1, U10.5
IN79: RN20.4, SW50.1, U10.6
IN80: RN21.1, SW51.1, U11.11
IN81: RN21.2, SW52.1, U11.12
IN82: RN21.3, SW53.1, U11.13
IN83: RN21.4, SW54.1, U11.14
IN84: RN22.1, SW55.1, U11.3
IN85: RN22.2, SW56.1, U11.4
IN86: RN22.3, SW57.1, U11.5
IN87: RN22.4, SW58.1, U11.6
IN88: RN23.1, SW59.1, U12.11
IN89: RN23.2, SW60.1, U12.12
IN90: RN23.3, SW61.1, U12.13
IN91: J1.1, RN23.4, U12.14
LED1: D1.4, D2.2
LED2: D2.4, D3.2
LED3: D3.4, D4.2
LED4: D4.4, D5.2
LED5: D5.4, D6.2
LED6: D6.4, D7.2
LED7: D7.4, D8.2
LED8: D8.4, D9.2
LED9: D9.4, D10.2
LED10: D10.4, D11.2
LED11: D11.4, D12.2
LED12: D12.4, D13.2
LED13: D13.4, D14.2
LED14: D14.4, D15.2
LED15: D15.4, D16.2
LED16: D16.4, D17.2
LED17: D17.4, D18.2
LED18: D18.4, D19.2
LED19: D19.4, D20.2
LED20: D20.4, D21.2
LED21: D21.4, D22.2
LED22: D22.4, D23.2
LED23: D23.4, D24.2
LED24: D24.4, D25.2
LED25: D25.4, D26.2
LED26: D26.4, D27.2
LED27: D27.4, D28.2
LED28: D28.4, D29.2
LED29: D29.4, D30.2
LED30: D30.4, D31.2
LED31: D31.4, D32.2
LED32: D32.4, D33.2
LED33: D33.4, D34.2
LED34: D34.4, D35.2
LED35: D35.4, D36.2
LED36: D36.4, D37.2
LED37: D37.4, D38.2
LED38: D38.4, D39.2
LED39: D39.4, D40.2
LED40: D40.4, D41.2
LED41: D41.4, D42.2
LED_3V3: U15.21, U16.2
LED_BUF: R19.1, U16.3
LED_DIN0: D1.2, R19.2
MUX_S0: U13.10, U14.10, U15.9
MUX_S1: U13.11, U14.11, U15.10
MUX_S2: U13.14, U14.14, U15.11
MUX_S3: U13.13, U14.13, U15.12
PAD0: FSR1.2, R1.1, U13.9
PAD1: FSR2.2, R2.1, U13.8
PAD2: FSR3.2, R3.1, U13.7
PAD3: FSR4.2, R4.1, U13.6
PAD4: FSR5.2, R5.1, U13.5
PAD5: FSR6.2, R6.1, U13.4
PAD6: FSR7.2, R7.1, U13.3
PAD7: FSR8.2, R8.1, U13.2
PAD8: FSR9.2, R9.1, U13.23
PAD9: FSR10.2, R10.1, U13.22
PAD10: FSR11.2, R11.1, U13.21
PAD11: FSR12.2, R12.1, U13.20
PAD12: FSR13.2, R13.1, U13.19
PAD13: FSR14.2, R14.1, U13.18
PAD14: FSR15.2, R15.1, U13.17
PAD15: FSR16.2, R16.1, U13.16
PADS_ADC: U13.1, U15.31
SR_CLK: U1.2, U2.2, U3.2, U4.2, U5.2, U6.2, U7.2, U8.2, U9.2, U10.2, U11.2, U12.2, U15.4
SR_DATA: U1.9, U15.6
SR_LOAD: U1.1, U2.1, U3.1, U4.1, U5.1, U6.1, U7.1, U8.1, U9.1, U10.1, U11.1, U12.1, U15.7

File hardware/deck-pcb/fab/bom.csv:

Qty,References,Value,Footprint,Side,Manufacturer,Part,Notes
16,FSR1 FSR2 FSR3 FSR4 FSR5 FSR6 FSR7 FSR8 FSR9 FSR10 FSR11 FSR12 FSR13 FSR14 FSR15 FSR16,,PinHeader_1x02_P2.54mm_Vertical,top (hand),,,Interlink FSR 402 Short: its two solder tabs go through these holes
1,J1,,PinHeader_1x04_P2.54mm_Vertical,top (hand),,,"1 x 4 pin header, 2.54 mm, to the pedal jacks"
8,RV1 RV2 RV3 RV4 RV5 RV6 RV7 RV8,,Potentiometer_Bourns_PTA4543_Single_Slide,top (hand),,,"Bourns PTA4543-2015DPB103 slide fader, 45 mm, 10 kOhm linear"
10,ENC1 ENC2 ENC3 ENC4 ENC5 ENC6 ENC7 ENC8 ENC9 ENC10,,RotaryEncoder_Alps_EC11E-Switch_Vertical_H20mm,top (hand),,,"Alps EC11E-series encoder with push switch, 20 detents, 20 mm shaft"
61,SW1 SW2 SW3 SW4 SW5 SW6 SW7 SW8 SW9 SW10 SW11 SW12 SW13 SW14 SW15 SW16 SW17 SW18 SW19 SW20 SW21 SW22 SW23 SW24 SW25 SW26 SW27 SW28 SW29 SW30 SW31 SW32 SW33 SW34 SW35 SW36 SW37 SW38 SW39 SW40 SW41 SW42 SW43 SW44 SW45 SW46 SW47 SW48 SW49 SW50 SW51 SW52 SW53 SW54 SW55 SW56 SW57 SW58 SW59 SW60 SW61,,SW_PUSH_6mm,top (hand),,,6 x 6 mm through-hole tactile switch (Omron B3F-1000 family; pick the height that meets the caps)
1,C79,1000u 10V,CP_Elec_8x10,bottom (machine),,,"1000 uF 10 V aluminium electrolytic, 8 x 10 mm SMD"
57,C1 C2 C3 C4 C5 C6 C7 C8 C9 C10 C11 C12 C13 C14 C15 C16 C17 C18 C19 C20 C21 C22 C23 C24 C25 C26 C27 C28 C29 C30 C31 C32 C33 C34 C35 C36 C37 C38 C39 C40 C41 C42 C43 C44 C45 C46 C47 C48 C49 C50 C51 C52 C53 C54 C75 C76 C78,100n,C_0603_1608Metric,bottom (machine),Samsung,CL10B104KB8NNNC,
20,C55 C56 C57 C58 C59 C60 C61 C62 C63 C64 C65 C66 C67 C68 C69 C70 C71 C72 C73 C74,10n,C_0603_1608Metric,bottom (machine),Samsung,CL10B103KB8NNNC,
1,C77,10u,C_0805_2012Metric,bottom (machine),Samsung,CL21A106KAYNNNE,
42,D1 D2 D3 D4 D5 D6 D7 D8 D9 D10 D11 D12 D13 D14 D15 D16 D17 D18 D19 D20 D21 D22 D23 D24 D25 D26 D27 D28 D29 D30 D31 D32 D33 D34 D35 D36 D37 D38 D39 D40 D41 D42,SK6812MINI-E,LED_SK6812MINI-E_3.2x2.8mm_P1.5mm_ReverseMount,bottom (machine),Opsco,SK6812MINI-E,
16,R1 R2 R3 R4 R5 R6 R7 R8 R9 R10 R11 R12 R13 R14 R15 R16,10k,R_0603_1608Metric,bottom (machine),Yageo,RC0603FR-0710KL,
1,R17,1k,R_0603_1608Metric,bottom (machine),Yageo,RC0603FR-071KL,
1,R18,100k,R_0603_1608Metric,bottom (machine),Yageo,RC0603FR-07100KL,
1,R19,330,R_0603_1608Metric,bottom (machine),Yageo,RC0603FR-07330RL,
23,RN1 RN2 RN3 RN4 RN5 RN6 RN7 RN8 RN9 RN10 RN11 RN12 RN13 RN14 RN15 RN16 RN17 RN18 RN19 RN20 RN21 RN22 RN23,4x10k,R_Array_Convex_4x0603,bottom (machine),Yageo,YC164-JR-0710KL,
1,U15,Pico 2,RaspberryPi_Pico_SMD,bottom (machine),Raspberry Pi,"Pico 2 (RP2350), soldered by its castellations",
1,U16,74AHCT125,SOIC-14_3.9x8.7mm_P1.27mm,bottom (machine),Texas Instruments,SN74AHCT125DR,
12,U1 U2 U3 U4 U5 U6 U7 U8 U9 U10 U11 U12,74HC165,SOIC-16_3.9x9.9mm_P1.27mm,bottom (machine),Texas Instruments,SN74HC165DR,
2,U13 U14,74HC4067,SOIC-24W_7.5x15.4mm_P1.27mm,bottom (machine),Texas Instruments,CD74HC4067M96,

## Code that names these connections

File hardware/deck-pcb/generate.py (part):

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
# The pedal jacks' header, top side, by the right-hand rear corner.
fp = add("Connector_PinHeader_2.54mm", "PinHeader_1x04_P2.54mm_Vertical", "J", "PEDALS", 300, 182, 90,
         pins={"1": inp(input_of[("Sustain", "pedal")]), "2": "EXPR", "3": "EXPR_RING", "4": "GND"})
claim(fp, "top")
pedal_at = (300, 182)

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    cid = c["id"]
    kind, x, y, w, h = panel[cid]
    k = c["light"]
    pins = {"1": "GND", "2": "LED_DIN0" if k == 0 else f"LED{k}", "3": "+5V", "4": f"LED{k + 1}"}
    # (x, y, angle) to try in turn.
    if kind == "pad":
        spots = [(x + 9, y - 10.5, 0), (x - 9, y - 10.5, 0)]
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    spots = [where(cid) if cid in panel else pedal_at for cid, _ in members]
    cx = sum(p[0] for p in spots) / len(spots)
    cy = sum(p[1] for p in spots) / len(spots)
    pins = {"1": "SR_LOAD", "2": "SR_CLK", "8": "GND", "15": "GND", "16": "+3V3",
            "9": "SR_DATA" if k == 0 else f"CHAIN{k}", "10": f"CHAIN{k + 1}" if k < CHIPS - 1 else "GND"}
    # D0..D7 are pins 11, 12, 13, 14, 3, 4, 5, 6: input A..H.
    for bit, pin in enumerate(["11", "12", "13", "14", "3", "4", "5", "6"]):
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# The two multiplexers. 4067: COM 1, I7..I0 on 2..9, S0 10, S1 11, GND 12,
# S3 13, S2 14, E 15, I15..I8 on 16..23, VCC 24.
def mux_pins(channel_net, com):
    pins = {"1": com, "10": "MUX_S0", "11": "MUX_S1", "12": "GND", "13": "MUX_S3", "14": "MUX_S2", "15": "GND", "24": "+3V3"}
    for ch in range(16):
        pin = 9 - ch if ch < 8 else 23 - (ch - 8)
        pins[str(pin)] = channel_net(ch)
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

u13 = place_bottom("Package_SO", "SOIC-24W_7.5x15.4mm_P1.27mm", "U", "74HC4067", 159, 228,
                   pins=mux_pins(lambda ch: f"PAD{ch}", "PADS_ADC"))
place_bottom("Capacitor_SMD", "C_0603_1608Metric", "C", "100n", u13.GetPosition().x / MM, u13.GetPosition().y / MM - 10,
             pins={"1": "+3V3", "2": "GND"}, radius=15)
u14 = place_bottom("Package_SO", "SOIC-24W_7.5x15.4mm_P1.27mm", "U", "74HC4067", 159, 165,
                   pins=mux_pins(lambda ch: f"FADER{ch}" if ch < 8 else ("EXPR" if ch == 8 else "GND"), "FADERS_ADC"))
place_bottom("Capacitor_SMD", "C_0603_1608Metric", "C", "100n", u14.GetPosition().x / MM, u14.GetPosition().y / MM - 10,
             pins={"1": "+3V3", "2": "GND"}, radius=15)

# The expression pedal: 1 kΩ in the supply to its ring, 100 kΩ holding the
# tip down when nothing is plugged in.
place_bottom("Resistor_SMD", "R_0603_1608Metric", "R", "1k", pedal_at[0], pedal_at[1] + 6, pins={"1": "+3V3", "2": "EXPR_RING"}, radius=15)
place_bottom("Resistor_SMD", "R_0603_1608Metric", "R", "100k", pedal_at[0], pedal_at[1] + 9, pins={"1": "EXPR", "2": "GND"}, radius=15)

# The Pico 2, bottom side, castellated. Pins as on the schematics.
pico_pins = {"4": "SR_CLK", "6": "SR_DATA", "7": "SR_LOAD", "9": "MUX_S0", "10": "MUX_S1", "11": "MUX_S2",
             "12": "MUX_S3", "21": "LED_3V3", "31": "PADS_ADC", "32": "FADERS_ADC", "33": "GND", "36": "+3V3",
             "40": "+5V"}
for g in ["3", "8", "13", "18", "23", "28", "38"]:
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# The LED level shifter: GP16 through gate 1 of a 74AHCT125 at 5 V, then
# 330 Ω into the first LED. The other three gates are tied off.
place_bottom("Package_SO", "SOIC-14_3.9x8.7mm_P1.27mm", "U", "74AHCT125", led_at[0][0] + 10, led_at[0][1] + 8,
             pins={"1": "GND", "2": "LED_3V3", "3": "LED_BUF", "4": "+5V", "5": "GND", "7": "GND", "9": "GND",
                   "10": "+5V", "12": "GND", "13": "+5V", "14": "+5V"}, radius=30)
place_bottom("Capacitor_SMD", "C_0603_1608Metric", "C", "100n", led_at[0][0] + 10, led_at[0][1] + 15, pins={"1": "+5V", "2": "GND"}, radius=20)
place_bottom("Resistor_SMD", "R_0603_1608Metric", "R", "330", led_at[0][0] + 4, led_at[0][1] + 8, pins={"1": "LED_BUF", "2": "LED_DIN0"}, radius=20)
place_bottom("Capacitor_SMD", "CP_Elec_8x10", "C", "1000u 10V", led_at[0][0] + 20, led_at[0][1] + 12, pins={"1": "+5V", "2": "GND"}, radius=40)

# ── Outline ──────────────────────────────────────────────────────────────
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
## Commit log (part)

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2026-03-21 Initial release: terminal-native DAW with per-track polyphonic synth
    - 6-crate workspace: core, dsp, midi, plugin, tui, gui
    - Real-time audio engine with lock-free mixer (cpal backend)
    - 16-voice polyphonic subtractive synth with dual oscillators,
    SVF filter, drive, sub osc, noise, full ADSR envelope
    - MIDI auto-detection with SPSC ring buffer routing
    - Per-track instrument instances with independent parameters
2026-03-21 Add crates.io publish metadata and LICENSE
    - Add description, repository, license, keywords, categories to all crates
    - Add version numbers to workspace internal dependencies
    - Add MIT LICENSE file
    - Publish order: plugin → midi → dsp → core → gui → tui → phosphor
2026-03-21 Refactor: split TUI state module, eliminate type duplication, remove dead code
    - Split state.rs (1,394 lines) into 5 focused modules:
    state/mod.rs, track.rs, menu.rs, clip_view.rs, input.rs
    - Delete TrackType enum, use TrackKind from phosphor-core everywhere
    - Remove dead fields: Clip.volume, Clip.fx_chain, Clip.midi_notes,
    TrackState.route, AudioRoute enum, MidiNote struct
    - Remove space_menu_select() (duplicated space_menu_handle logic)
2026-03-21 Add measure-locked loop recording
    - Transport: start_loop_record() / stop_loop_record() for one-key workflow
    - Transport: set_loop_bars() for bar-based loop range
    - Mixer: detect loop wrap via tick position comparison, auto-commit clip
    - Mixer: start new recording pass on loop wrap (foundation for overdub)
    - RecordBuffer: expose start_tick() for wrap detection
    - TUI: R (shift+r) toggles loop recording on selected track
2026-03-21 Fix all clippy warnings in ui.rs
    - Add TrackCtx struct to bundle render args (9 args → 3)
    - Refactor render_track_row, render_header, render_clips to use TrackCtx
    - Replace indexed loops with iterator patterns (grid.iter_mut(), slice get_mut)
    - Replace manual range check with RangeInclusive::contains
    - Replace indexed synth param loop with iter().enumerate().skip().take()
    cargo clippy --workspace now produces zero warnings.
2026-03-21 Separate loop region editing from loop activation
    - Space+l focuses the loop editor (set markers) but does NOT enable looping
    - Enter while in loop editor toggles loop on/off
    - Transport only loops when explicitly activated via Enter
    - Top bar shows: "loop?[1-4]" when editing but not active,
    "loop[1-4]" when editing and active, "loop:1-4" when active,
    "loop:off" when disabled
2026-03-21 Start playback from loop start when loop is enabled
2026-03-21 Add action map and scenario-based test harness
    - New actions.rs: every user action as an enum (50+ variants)
    - New test_harness.rs: headless App testing with action sequences
    - App.execute_action(): single method that maps actions to state changes
    - 11 scenario tests covering:
    - Set loop region and activate
    - Play starts at loop start when loop enabled
2026-03-21 Silence all instruments when playback stops
    When the user pauses, stops, or ends loop recording, all synth
    voices are reset immediately via the panic flag. Prevents notes
    from ringing after the transport stops.
    Found via debug log: pausing mid-clip-playback left synth voices
    in sustain state with no way to release them except manual panic.
2026-03-21 Display recorded MIDI notes in the piano roll
    - Piano roll now draws NoteSnapshot data from the active clip
    - Notes rendered as colored blocks in track color on the grid
    - When selecting a track with clips, piano roll tab auto-focuses
    - Selecting a clip via Enter opens piano roll with that clip's notes
    - Tracks without clips still show synth controls panel
2026-03-21 Fix BPM control, space menu columns, clip note debug logging
    - BPM +/- now works globally (any pane, not just tracks)
    - Space menu renders in columns to use horizontal space
    - Space menu tab bar shows +/- bpm hint
    - Debug log: clip snapshots log note count and tick range on receive
    - Metronome indicator (musical note) shows in top bar
2026-03-21 Fix transport pane visibility and BPM controls
    - BPM +/- now works in ALL contexts (removed track_selected guard on -)
    - Transport pane shows highlighted BPM with "+bpm-" label when focused
    - BPM value gets bright yellow background when transport is focused
    - focus_pane() now logs the pane change for debug visibility
    - Bottom bar shows tab/spc/+/- hints when transport is focused
2026-03-21 Add transport element navigation (BPM, Record, Loop, Metronome)
    - New TransportUiState with navigable TransportElement enum
    - h/l navigates between BPM, Record, Loop, Metronome in transport
    - Enter on BPM → locks h/l to adjust tempo (same pattern as loop editor)
    - Enter on Record → toggles recording
    - Enter on Loop → opens loop editor
    - Enter on Metronome → toggles click track
2026-03-22 Size tracks area to actual track count, not fixed max — buffer 3 fills remaining space
2026-03-22 Track name in first bar at bottom row, bold track color
2026-03-22 Track divider on all bars except first, name visible in first bar
    - Bottom row of each track: divider line from bar 2 onward
    - First bar bottom row: track name in bold track color (no divider)
    - Header last row also shows divider line for visual consistency
    - Tracks are clearly separated while name remains visible
2026-03-22 Piano roll column navigation with focus hierarchy
    - 3-level focus: Browsing → Column → Row (Enter deeper, Esc back)
    - Column mode: numbered columns at top, h/l moves between columns,
    number keys jump to column (smart: waits for second digit if ambiguous)
    - Row mode: j/k navigates notes within column, h/l and H/L reserved
    for future note edge editing (same pattern as loop editor)
    - Selected column highlighted with subtle background tint
2026-03-22 Note editing syncs to audio thread — edits affect playback
    Data flow: edit NoteSnapshot → convert to ClipEvents → MixerCommand::UpdateClip → audio thread replaces clip
    New:
    - NoteSnapshot::to_clip_events(): converts edited notes back to MIDI events
    - MixerCommand::UpdateClip: replaces a clip's events on the audio thread
    - send_clip_update(): called after every note edit, pushes to audio
    - adjust_column_edges(): edits ALL notes in a column (Shift+h/l in column mode)
2026-03-22 Implement Right Left Trick Controls for piano roll
    The standard Phosphor control pattern, now properly applied:
    Browsing (h/l = navigate columns, Enter = select):
    h/l moves between columns, number keys jump, Enter selects
    Column selected (controls locked):
    h/l = adjust LEFT edge of ALL notes in column
    H/L = adjust RIGHT edge of ALL notes in column
2026-03-22 Reset piano roll state when switching tracks
    - Column resets to 1 when selecting a track with clips
    - Focus resets to Browsing mode (not stuck in Column/Row from previous)
    - Fixes "random column selected" issue when re-entering piano roll
2026-03-22 Fix notes escaping column during editing
    Root cause: adjust_column_edges rescanned column range each edit,
    but moving start_frac pushed notes outside the column boundary,
    making subsequent edits find 0 notes.
    Fix: capture note indices when column is selected (Enter). All
    subsequent edits operate on those stored indices regardless of
    where the notes drift. Notes stay "selected" until Esc.
2026-03-22 Tab cycles through ALL buffer 3 tabs, n draws notes
    Tab cycling: trk fx → synth → piano → auto → trk fx (full loop)
    Previously Tab only cycled within the current panel side.
    Draw notes: press n in Row mode to create a new note at the
    current cursor position (column + pitch). Default velocity 100,
    default duration one column wide. Syncs to audio thread.
    Bottom bar shows n·draw keybind in Row mode.
2026-03-22 Auto-create clip when drawing notes on empty track
    draw_note() was silently failing because active_clip_mut()
    returned None when the track had no clips (never recorded).
    Now: if no clip exists when n is pressed, one is created
    automatically using the loop region length. The clip gets
    added to the track, clip_view_target is updated, and the
    note is inserted into the new clip.
2026-03-22 Fix notes not playing on loop repeat
    When the transport loops, position jumps from ~15350 to ~1, skipping
    tick 0. Notes at the loop start fell in the gap and never played on
    subsequent passes.
    Fix: detect the wrap (current_tick < last_tick) and play events from
    loop_start through current position on the first buffer after a wrap.
    This catches any notes at the loop boundary.
2026-03-22 Fix recorded clip spanning full loop region
    Recording started at current_tick (e.g., tick 12) instead of
    loop_start (tick 0), making the clip shorter than the loop region.
    A 2-bar loop produced a clip of 7668 ticks instead of 7680.
    Fix: when loop recording, start the record buffer at loop_start
    so the clip spans the full loop region regardless of when the
    first note was played.
2026-03-23 Add synthesized drum rack — 808, 909, 707, 606 kits
    New DrumRack plugin (phosphor-dsp/drum_rack.rs):
    - 4 classic drum machine kits, switchable via parameter 0 (same
    pattern as synth waveform selector, 0.25 steps)
    - All sounds synthesized — no samples, pure math
    - MIDI notes 36-56 mapped to: kick, rim, snare, clap, closed hat,
    low/mid/high tom, open hat, crash, ride, cowbell
2026-03-23 Full drum rack rewrite — 88 sounds per kit, 5 synthesis engines
    Complete rewrite of the drum rack with proper sound variety:
    5 synthesis engines (reusable building blocks):
    1. SineBody — pitched sine + pitch sweep (kicks, toms)
    2. NoiseBurst — band-passed noise (snares, hats, crashes)
    3. Click — sharp impulse (rims, claves, blocks)
    4. Metallic — two detuned sines (cowbell, ride, agogo)
2026-03-23 Add 777 kit — 808/909 bass octaves + creative original sounds
    New 5th drum kit preserving the original bass sounds:
    - Notes 24-35: 808-style bass (42Hz sine, heavy 9x sweep, long decay)
    Full octave from deep 25Hz sub to 59Hz punch
    - Notes 36-47: 909-style bass (58Hz distorted sine, noise click)
    Full octave with waveshaping and click transients
    Original 777 sounds (not copies of other kits):
2026-03-23 Bump version to 0.2.0 for crates.io publish
2026-03-24 Add ARP Odyssey + Jupiter-8 synths, expand all patch libraries to 137 total
    New instruments:
    - Jupiter-8: 8-voice poly with IR3109 OTA ladder filter (tanh saturation),
    dual polyBLEP VCOs, exponential envelopes, global LFO, 4 voice modes
    (solo/unison/poly1/poly2), per-voice analog drift. 42 patches from
    Roland factory sheets and programming guides.
    - ARP Odyssey: Duophonic synth with 3 selectable filter types
2026-03-25 v0.3.0 — Juno-60, session save/load, 10 drum kits, 300+ patches
    New instruments:
    - Juno-60: Single DCO per voice with BBD stereo chorus (I/II/I+II),
    sub-oscillator, 4-position HPF, single shared ADSR. 18 patches.
    Session save/load system:
    - .phos file format (human-readable JSON, atomic writes)
    - Ctrl+S quick save, Space+S save-as, Space+O open
2026-03-25 save point
2026-03-26 Bump version to 0.3.2
2026-04-02 v0.3.4 — Piano roll edit mode, note stretching, phantom fix, grid rendering
    Edit mode (Space+E):
    - Navigate between individual notes with column-locked j/k and h/l
    - Enter selects a single note, Shift+direction selects multiple
    - Plain h/l/j/k moves selected notes by grid step / semitone
    - Shift+H/L stretches right edge, Shift+J/K stretches left edge
    - d deletes cursor note or selected group, u undoes, all synced to audio
